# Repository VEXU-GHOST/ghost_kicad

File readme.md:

# VEXU GHOST PCB Repository

Welcome to UT IEEE RAS VEXU GHOST's repository for our PCB developments!
- [PCB Images](docs/pcb_images.md)
- [Onboarding](docs/onboarding.md)

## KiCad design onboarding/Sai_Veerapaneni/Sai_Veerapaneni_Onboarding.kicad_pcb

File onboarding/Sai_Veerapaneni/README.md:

# Sai Veerapaneni — PCB onboarding

Open `Sai_Veerapaneni_Onboarding.kicad_pro` in KiCad 10 to review the
color-sensor schematic and completed two-layer PCB.

The board is 26 × 18 mm, with 14 footprints, routed signal and supply nets,
front/back GND pours, and a rectangular Edge.Cuts outline. Signal tracks
are 0.2 mm; supply tracks are 0.3 mm with 0.2 mm sensor escapes. Copper
clearance is 0.2 mm and copper-to-edge clearance is 0.5 mm.

J1 pinout: **1 GND, 2 SCL, 3 SDA, 4 +3.3V, 5 +5V**. The host provides
both regulated supply rails. Sai Veerapaneni is printed on the back silk.

Custom libraries are project-local. Standard footprints and 3D models
use the installed KiCad libraries and this repository's `ghost_library`.
The connector preserves standard pads, drills, and physical geometry;
its off-board lead artwork is on F.Fab to keep silk inside the board edge.

Validation reports are saved in `checks/`. The schematic follows the
onboarding reference without power flags; the three external-supply ERC
errors are the ones the onboarding explicitly permits ignoring.

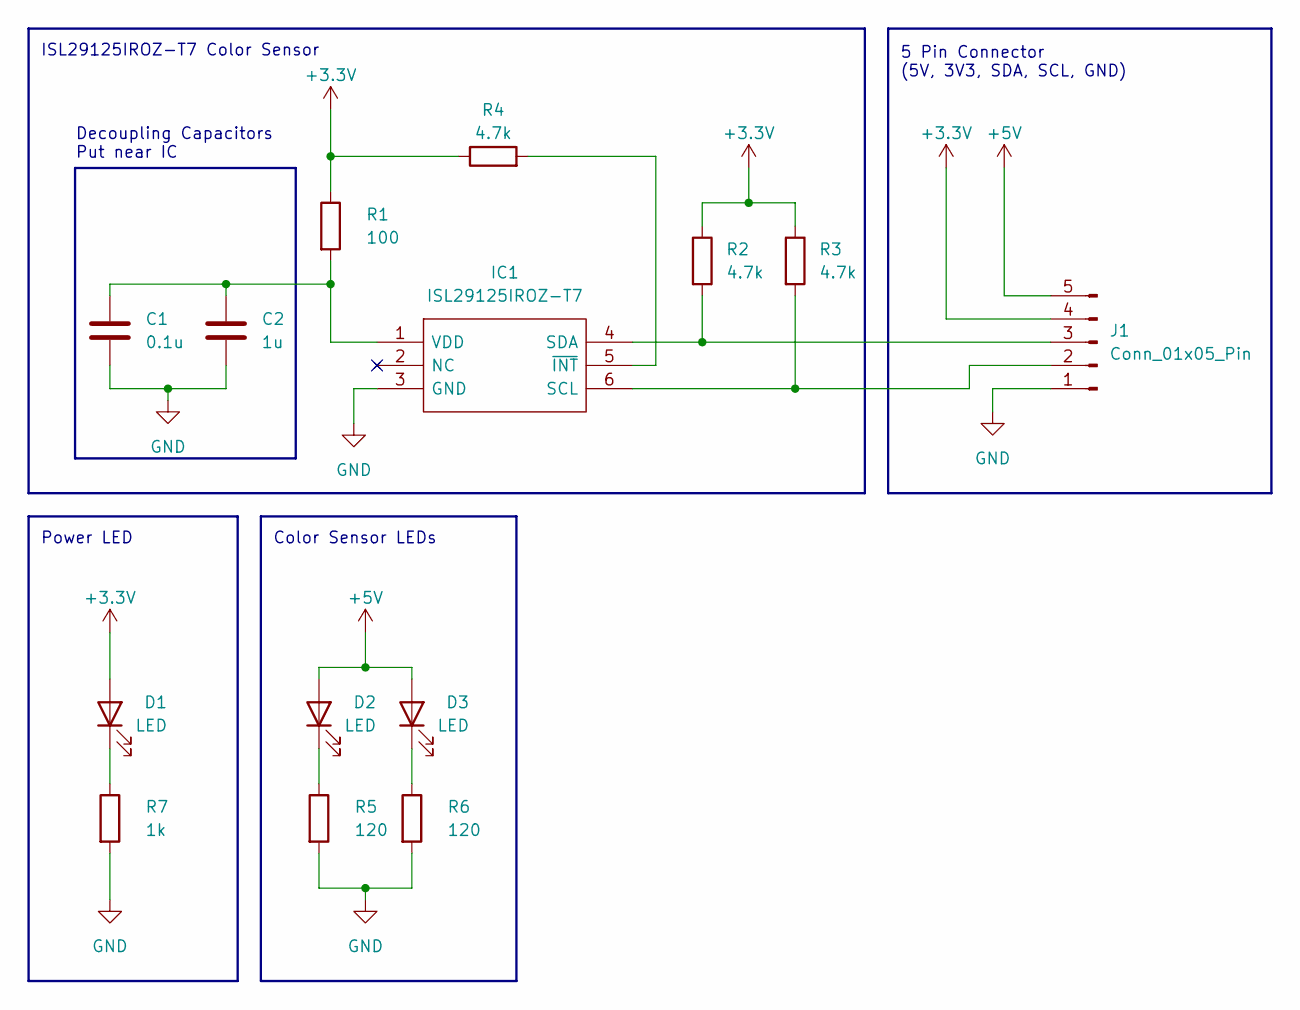
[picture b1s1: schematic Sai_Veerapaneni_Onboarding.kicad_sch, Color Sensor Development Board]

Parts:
C1: 0.1u; C_0603_1608Metric_Pad1.08x0.95mm_HandSolder
C2: 1u; C_0603_1608Metric_Pad1.08x0.95mm_HandSolder
D1: LED; LED_0603_1608Metric_Pad1.05x0.95mm_HandSolder
D2, D3: LED; LED_0805_2012Metric_Pad1.15x1.40mm_HandSolder
IC1: ISL29125IROZ-T7; ISL29125IROZT7; Manufacturer_Part_Number ISL29125IROZ-T7; Mouser Part Number 968-ISL29125IROZ-T7
J1: Conn_01x05_Pin; PinHeader_1x05_P2.54mm_Horizontal
R1: 100; R_0603_1608Metric_Pad0.98x0.95mm_HandSolder
R2, R3, R4: 4.7k; R_0603_1608Metric_Pad0.98x0.95mm_HandSolder
R5, R6: 120; R_0603_1608Metric_Pad0.98x0.95mm_HandSolder
R7: 1k; R_0603_1608Metric_Pad0.98x0.95mm_HandSolder

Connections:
+3.3V: D1.2 (A), J1.4, R1.1, R2.1, R3.1, R4.1
+5V: D2.2 (A), D3.2 (A), J1.5
GND: C1.2, C2.2, IC1.3 (GND), J1.1, R5.2, R6.2, R7.2
unnamed: D1.1 (K), R7.1
unnamed: D2.1 (K), R5.1
unnamed: D3.1 (K), R6.1
unnamed: IC1.6 (SCL), J1.2, R3.2
unnamed: IC1.4 (SDA), J1.3, R2.2
unnamed: C1.1, C2.1, IC1.1 (VDD), R1.2
unnamed: IC1.5 (~INT), R4.2

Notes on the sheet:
Color Sensor LEDs
Power LED
Decoupling Capacitors Put near IC
ISL29125IROZ-T7 Color Sensor
5 Pin Connector (5V, 3V3, SDA, SCL, GND)

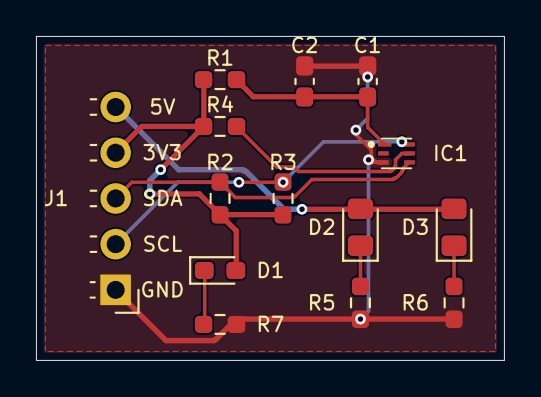
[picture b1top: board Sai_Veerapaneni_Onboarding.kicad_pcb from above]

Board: 2 copper layers, 26.0 x 18.0 mm, 14 parts (0 on the bottom side), 10 nets.

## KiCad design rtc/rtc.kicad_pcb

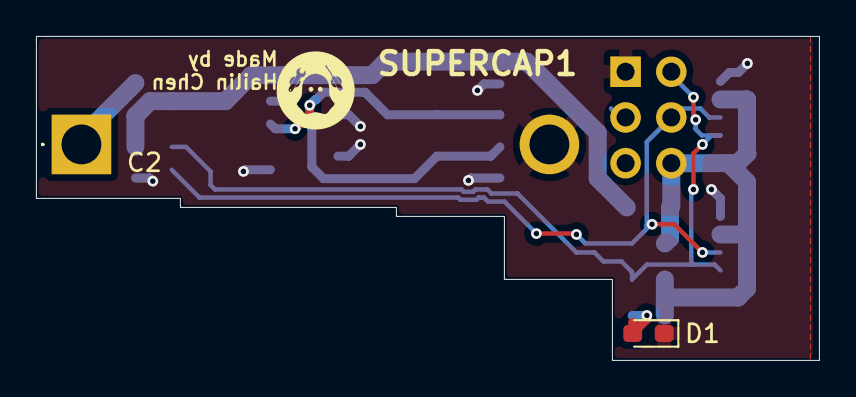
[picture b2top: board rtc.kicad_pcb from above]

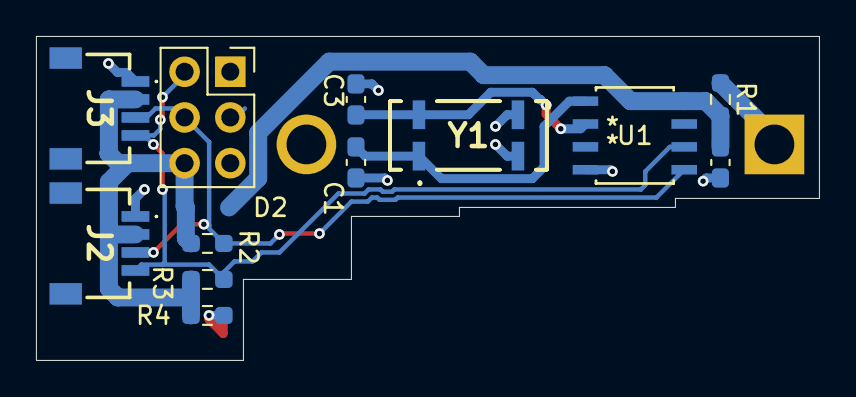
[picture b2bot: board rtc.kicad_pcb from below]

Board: 2 copper layers, 43.5 x 18.0 mm, 15 parts (13 on the bottom side), 9 nets.

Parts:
C1, C3: 24p; C_0603_1608Metric_Pad1.08x0.95mm_HandSolder
C2: 0.1u; C_0603_1608Metric_Pad1.08x0.95mm_HandSolder
D1: LED; LED_0603_1608Metric_Pad1.05x0.95mm_HandSolder
D2: RB751V-40X_R1; SODFL2512X90N
J1: Conn_02x03_Odd_Even; PinSocket_2x03_P2.54mm_Vertical
J2, J3: Conn_01x04; SM04BSRSSTB
R1: 20k; R_0603_1608Metric_Pad0.98x0.95mm_HandSolder
R2, R3, R4: 2.5k; R_0603_1608Metric_Pad0.98x0.95mm_HandSolder
SUPERCAP1: 5; CE5R5505HFZJ
U1: PCF8563T/5_518; PCF8563T_5_518_U_SO8_NXP
Y1: LFXTAL016178REEL

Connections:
+3.3V: D2.2 (A), J1.6, J2.2, J3.2, R2.2, R3.2, R4.1
GND: C1.2, C2.2, C3.2, D1.1 (K), J1.1, J2.1, J3.1, SUPERCAP1.2 (-), U1.4 (VSS), Y1.2 (N/C_1), Y1.3 (N/C_2)
unnamed: D1.2 (A), R4.2
unnamed: C2.1, D2.1 (K), R1.2, U1.8 (VDD)
unnamed: R1.1, SUPERCAP1.1 (+)
unnamed: C1.1, U1.1 (OSCI), Y1.1 (CRYSTAL_1)
unnamed: C3.1, U1.2 (OSCO), Y1.4 (CRYSTAL_2)
scl: J1.2, J2.4, J3.4, R3.1, U1.6 (SCL)
sda: J1.4, J2.3, J3.3, R2.1, U1.5 (SDA)

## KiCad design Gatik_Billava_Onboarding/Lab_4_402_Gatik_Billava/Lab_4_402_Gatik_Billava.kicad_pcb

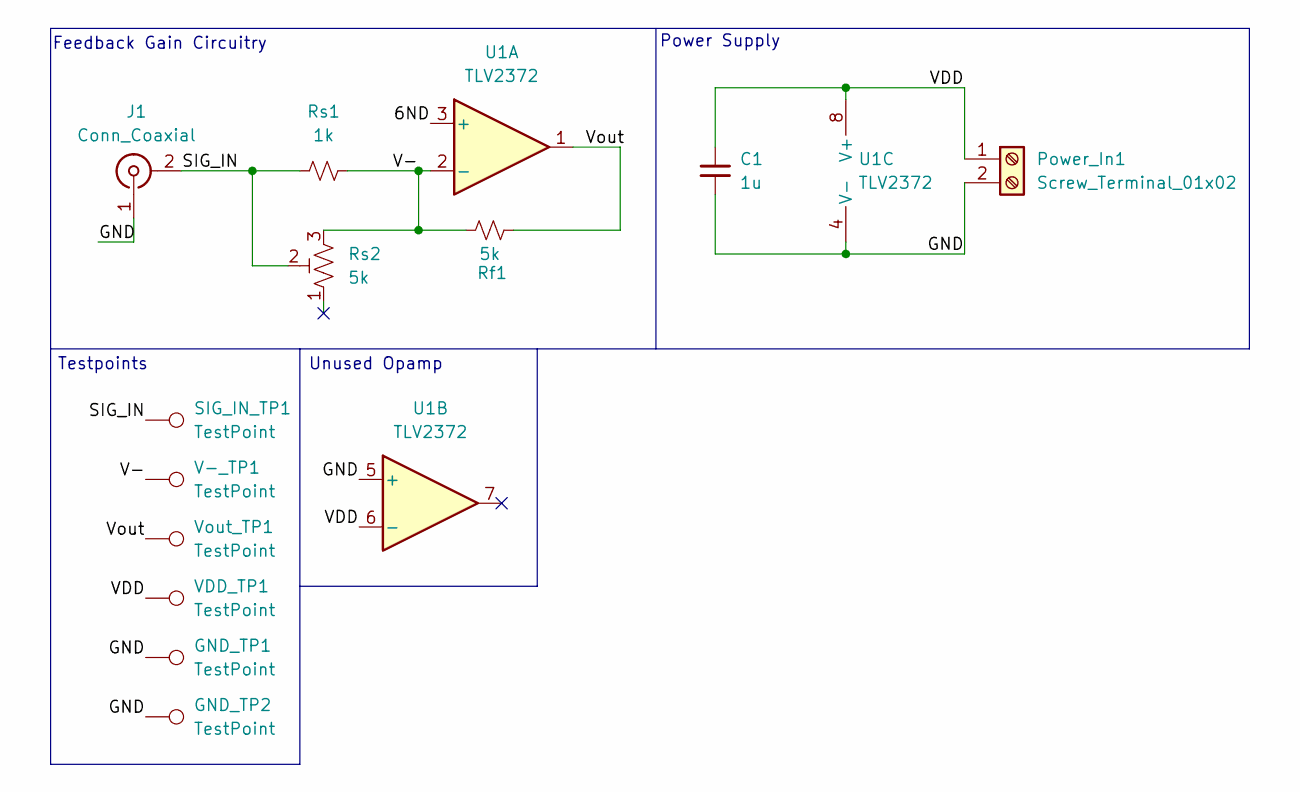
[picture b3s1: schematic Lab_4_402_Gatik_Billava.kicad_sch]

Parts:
C1: 1u; C_Disc_D3.8mm_W2.6mm_P2.50mm
GND_TP1, GND_TP2: TestPoint; TestPoint_Keystone_5010-5014_Multipurpose
J1: Conn_Coaxial; BNC_Amphenol_B6252HB-NPP3G-50_Horizontal
Power_In1: Screw_Terminal_01x02; PhoenixContact_MSTBA_2,5_2-G_1x02_P5.00mm_Horizontal
Rf1: 5k; R_Axial_DIN0207_L6.3mm_D2.5mm_P10.16mm_Horizontal
Rs1: 1k; R_Axial_DIN0207_L6.3mm_D2.5mm_P10.16mm_Horizontal
Rs2: 5k; Potentiometer_Vishay_43_Horizontal
SIG_IN_TP1: TestPoint; TestPoint_Keystone_5010-5014_Multipurpose
U1: TLV2372; SOIC-8_3.9x4.9mm_P1.27mm
V-_TP1: TestPoint; TestPoint_Keystone_5010-5014_Multipurpose
VDD_TP1: TestPoint; TestPoint_Keystone_5010-5014_Multipurpose
Vout_TP1: TestPoint; TestPoint_Keystone_5010-5014_Multipurpose

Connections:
/6ND: U1.3 (+)
/GND: C1.2, GND_TP1.1 (1_1), GND_TP2.1 (1_1), J1.1 (In), Power_In1.2, U1.4 (V-), U1.5 (+)
/SIG_IN: J1.2 (Ext), Rs1.1, Rs2.2, SIG_IN_TP1.1 (1_1)
/V-: Rf1.1, Rs1.2, Rs2.3, U1.2 (-), V-_TP1.1 (1_1)
/VDD: C1.1, Power_In1.1, U1.6 (-), U1.8 (V+), VDD_TP1.1 (1_1)
/Vout: Rf1.2, U1.1, Vout_TP1.1 (1_1)

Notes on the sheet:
Power Supply
Feedback Gain Circuitry
Unused Opamp
Testpoints

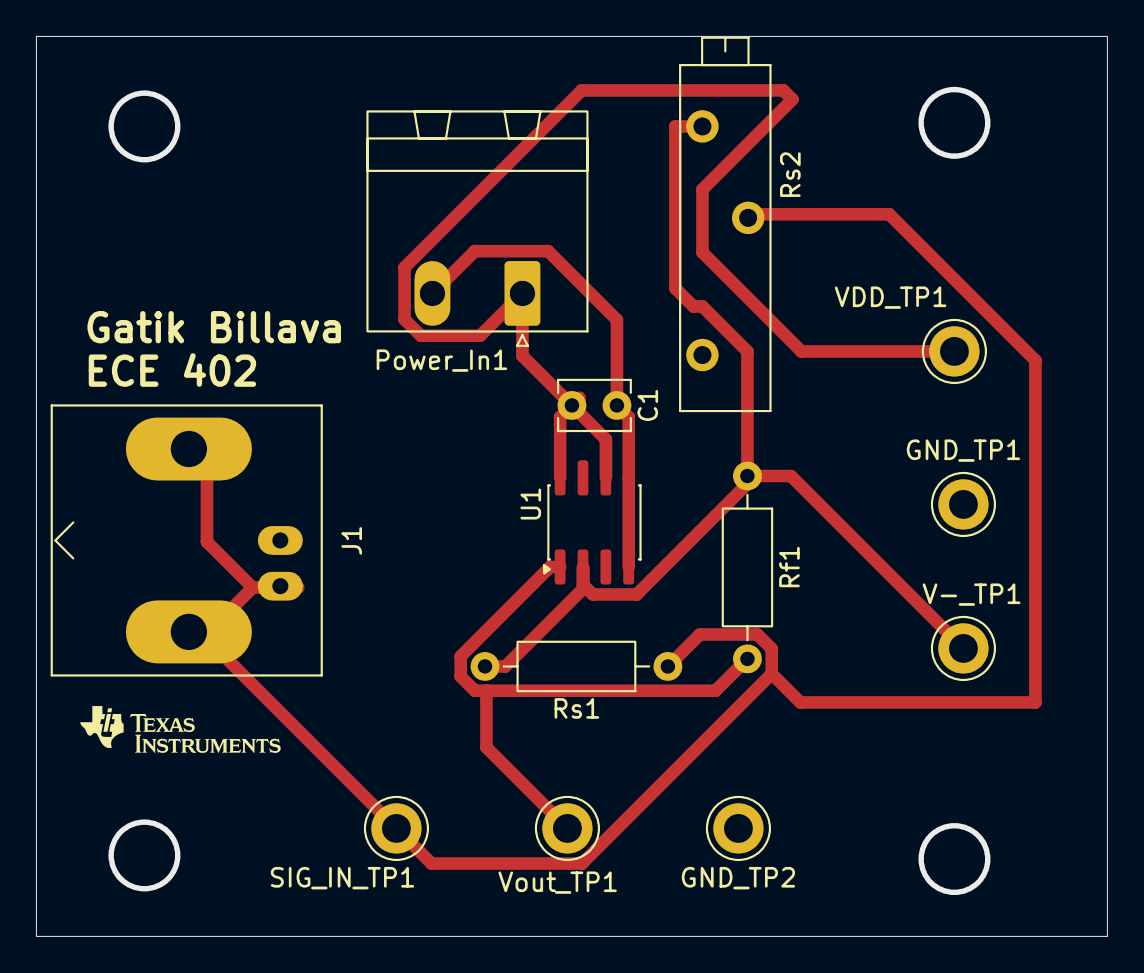
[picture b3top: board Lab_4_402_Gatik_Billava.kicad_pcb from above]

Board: 2 copper layers, 59.5 x 50.0 mm, 13 parts (0 on the bottom side), 5 nets.

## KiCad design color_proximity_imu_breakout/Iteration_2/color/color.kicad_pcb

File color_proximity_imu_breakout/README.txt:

color, imu, proximity.kicad files generated by hand from color+proximity.kicad_pcb

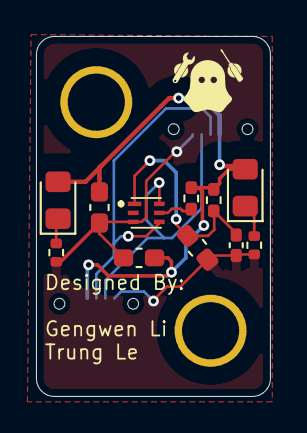
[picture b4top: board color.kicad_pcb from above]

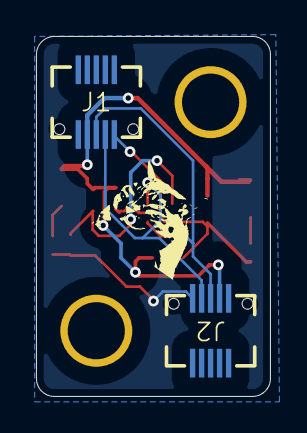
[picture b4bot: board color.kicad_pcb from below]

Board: 2 copper layers, 13.0 x 20.0 mm, 13 parts (2 on the bottom side), 8 nets.

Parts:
C1, C2: 10u; C_0603_1608Metric_Pad1.08x0.95mm_HandSolder
C4: 1u; C_0603_1608Metric_Pad1.08x0.95mm_HandSolder
C5: 0.1u; C_0402_1005Metric_Pad0.74x0.62mm_HandSolder
D1, D2: WHITE; LED_0805_2012Metric_Pad1.15x1.40mm_HandSolder
IC2: ISL29125IROZ-T7; ISL29125IROZT7
J1, J2: Conn_01x10; GT-B0502MSV27-10S1101
R15: 100; R_0402_1005Metric_Pad0.72x0.64mm_HandSolder
R16: 4.7k; R_0402_1005Metric_Pad0.72x0.64mm_HandSolder
R17, R18: 60; R_0402_1005Metric

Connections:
+3.3V: C1.1, C2.1, D1.2 (A), D2.2 (A), J1.7, J2.7, R15.2, R16.1
/scl: IC2.6 (SCL), J1.9, J2.9
/sda: IC2.4 (SDA), J1.8, J2.8
GND: C1.2, C2.2, C4.2, C5.2, IC2.3 (GND), J1.10, J2.10, R17.2, R18.2
unnamed: D1.1 (K), R17.1
unnamed: D2.1 (K), R18.1
unnamed: C4.1, C5.1, IC2.1 (VDD), R15.1
unnamed: IC2.5 (~INT), R16.2

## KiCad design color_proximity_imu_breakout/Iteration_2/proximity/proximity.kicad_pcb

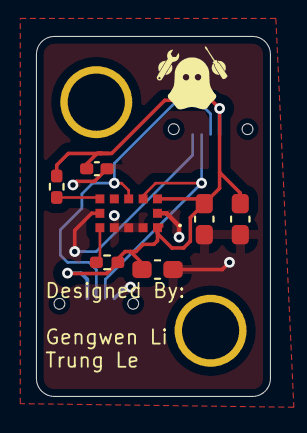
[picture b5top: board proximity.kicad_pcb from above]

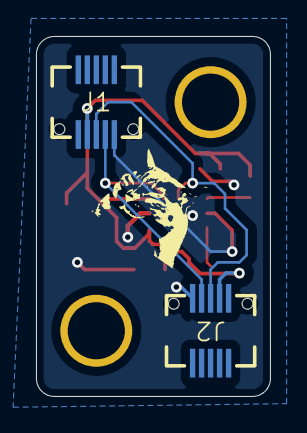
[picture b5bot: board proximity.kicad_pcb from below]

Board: 2 copper layers, 13.0 x 20.0 mm, 9 parts (2 on the bottom side), 6 nets.

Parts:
C1, C2: 10u; C_0603_1608Metric_Pad1.08x0.95mm_HandSolder
C11: 0.1u; C_0402_1005Metric_Pad0.74x0.62mm_HandSolder
C12: 4.7u; C_0603_1608Metric_Pad1.08x0.95mm_HandSolder
IC1: VL53L4CDV0DH_1; VL53L4CDV0DH1
J1, J2: Conn_01x10; GT-B0502MSV27-10S1101
R20, R21: 10k; R_0402_1005Metric_Pad0.72x0.64mm_HandSolder

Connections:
+3.3V: C1.1, C2.1, C11.1, C12.1, IC1.1 (AVDDVCSEL_1), IC1.11 (AVDD), IC1.13 (AVDDVCSEL_2), J1.7, J2.7, R20.2, R21.1
/scl: IC1.10 (SCL), J1.9, J2.9
/sda: IC1.9 (SDA), J1.8, J2.8
GND: C1.2, C2.2, C11.2, C12.2, IC1.2 (AVSSVCSEL), IC1.3 (GND), IC1.4 (GND2), IC1.6 (GND3), IC1.12 (GND4), J1.10, J2.10
unnamed: IC1.7 (GPIO1), R20.1
unnamed: IC1.5 (XSHUT), R21.2

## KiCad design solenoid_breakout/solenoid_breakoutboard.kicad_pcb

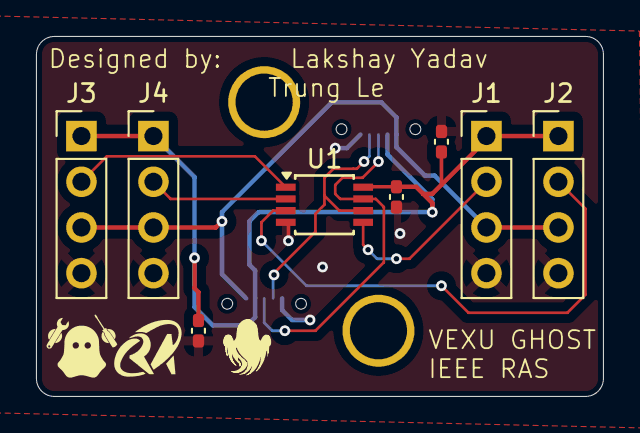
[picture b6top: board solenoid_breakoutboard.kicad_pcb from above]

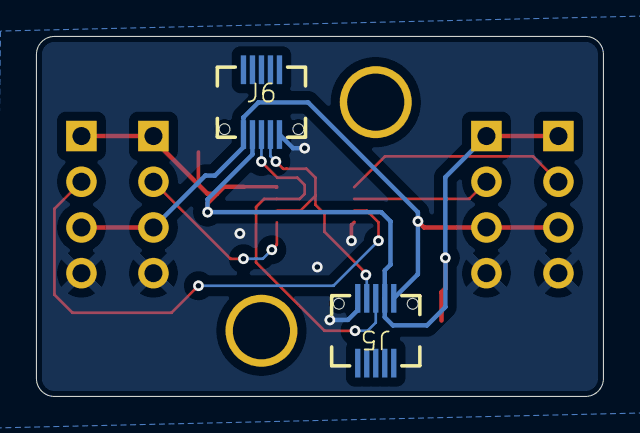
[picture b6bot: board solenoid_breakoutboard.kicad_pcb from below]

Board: 2 copper layers, 31.5 x 20.0 mm, 10 parts (2 on the bottom side), 9 nets.

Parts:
C1: 0.1uF; C_0402_1005Metric_Pad0.74x0.62mm_HandSolder
C2, C3: 10uF; C_0402_1005Metric_Pad0.74x0.62mm_HandSolder
J1, J2, J3, J4: Conn_01x04_Pin; PinHeader_1x04_P2.54mm_Vertical
J5, J6: Conn_01x10; GT-B0502MSV27-10S1101
U1: TCA9536DTMR; TSSOP-8_3x3mm_P0.65mm

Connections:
+3.3V: C1.1, C2.1, C3.1, J1.1, J2.1, J3.1, J4.1, J5.7, J6.7, U1.8 (VDD)
+5V: J1.3, J2.3, J3.3, J4.3, J5.6, J6.6
/scl: J5.9, J6.9, U1.6 (SCL)
/sda: J5.8, J6.8, U1.7 (SDA)
GND: C1.2, C2.2, C3.2, J1.4, J2.4, J3.4, J4.4, J5.10, J6.10, U1.4 (VSS)
unnamed: J1.2, U1.5 (IO3)
unnamed: J2.2, U1.3 (IO2)
unnamed: J3.2, U1.1 (IO0)
unnamed: J4.2, U1.2 (IO1)

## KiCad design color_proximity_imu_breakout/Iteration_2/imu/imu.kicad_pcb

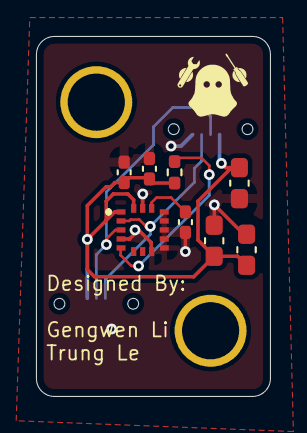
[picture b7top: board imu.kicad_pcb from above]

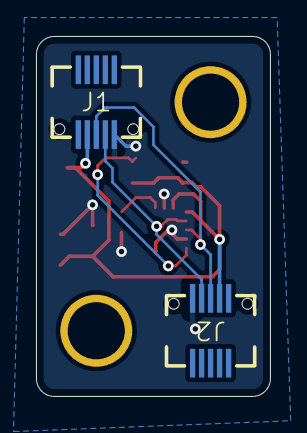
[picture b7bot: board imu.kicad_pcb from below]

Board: 2 copper layers, 13.0 x 20.0 mm, 10 parts (2 on the bottom side), 6 nets.

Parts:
C1, C2: 10u; C_0603_1608Metric_Pad1.08x0.95mm_HandSolder
C7, C10: 0.1u; C_0402_1005Metric_Pad0.74x0.62mm_HandSolder
C8: 2.2u; C_0603_1608Metric_Pad1.08x0.95mm_HandSolder
C9: 10n; C_0402_1005Metric_Pad0.74x0.62mm_HandSolder
J1, J2: Conn_01x10; GT-B0502MSV27-10S1101
R19: 4.7k; R_0402_1005Metric_Pad0.72x0.64mm_HandSolder
U6: ICM-20602; IAM20680HP

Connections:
+3.3V: C1.1, C2.1, C7.1, C8.1, C9.1, J1.7, J2.7, R19.1, U6.1 (VDDIO), U6.16 (VDD)
/scl: J1.9, J2.9, U6.2 (SCL/SPC)
/sda: J1.8, J2.8, U6.3 (SDA/SDI)
GND: C1.2, C2.2, C7.2, C8.2, C9.2, C10.2, J1.10, J2.10, U6.4 (SAO/SD0), U6.8 (FSYNC), U6.9 (GND), U6.10 (GND), U6.11 (GND), U6.12 (GND), U6.13 (GND), U6.15 (GND)
unnamed: C10.1, U6.14 (REGOUT)
unnamed: R19.2, U6.5 (~CS)

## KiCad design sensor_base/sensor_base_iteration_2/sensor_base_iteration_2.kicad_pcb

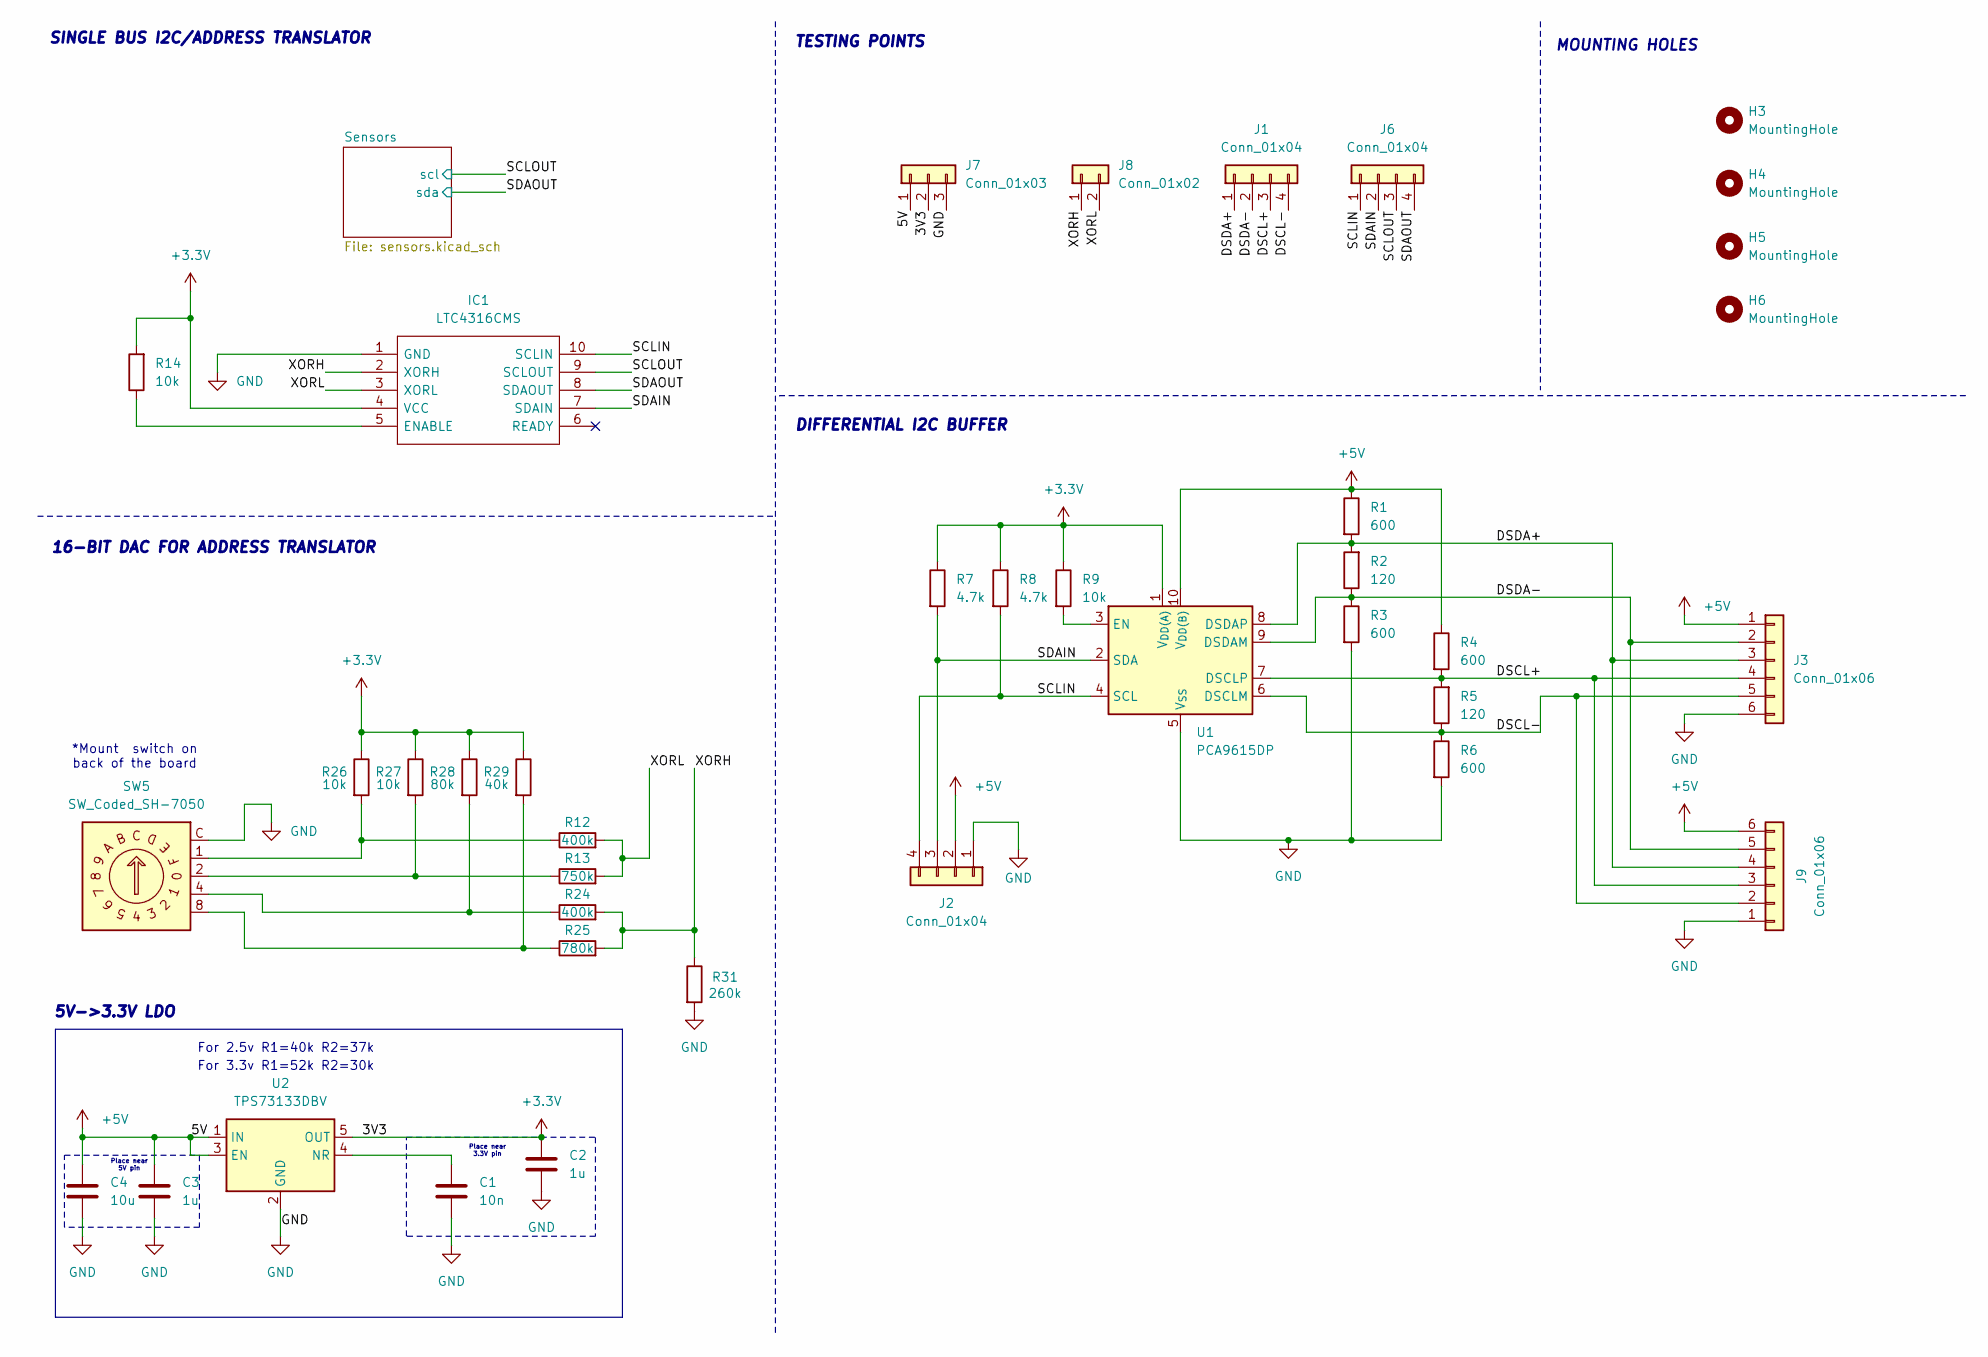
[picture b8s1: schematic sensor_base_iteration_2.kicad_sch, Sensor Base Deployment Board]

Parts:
C1: 10n; C_0402_1005Metric_Pad0.74x0.62mm_HandSolder; Manufacturer_Part_Number CL05B103KB5NNNC; JLCPCB Part C1523
C2, C3: 1u; C_0603_1608Metric_Pad1.08x0.95mm_HandSolder; Manufacturer_Part_Number CL10B105KB8NQNC; JLCPCB Part C15849
C4: 10u; C_0603_1608Metric_Pad1.08x0.95mm_HandSolder; Manufacturer_Part_Number CL10A106KP8NNNC; JLCPCB Part C15849
H3, H4, H5, H6: MountingHole; MountingHole_#4_3.175mm
IC1: LTC4316CMS; SOP50P490X110-10N; Manufacturer_Part_Number LTC4316CMS#TRPBF; Mouser Part Number 584-LTC4316CMS#TRPBF
J1, J6: Conn_01x04; PinHeader_1x04_P1.27mm_Vertical
J2: Conn_01x04; JST_GH_SM04B-GHS-TB_1x04-1MP_P1.25mm_Horizontal; Manufacturer_Part_Number XY-SM04B-GHS-TB; JLCPCB Part C51940130
J3, J9: Conn_01x06; JST_GH_SM06B-GHS-TB_1x06-1MP_P1.25mm_Horizontal; Manufacturer_Part_Number XY-SM06B-GHS-TB; JLCPCB Part C160405
J7: Conn_01x03; PinHeader_1x03_P1.27mm_Vertical
J8: Conn_01x02; PinHeader_1x02_P1.27mm_Vertical
R1, R3, R4, R6: 600; R_0402_1005Metric_Pad0.72x0.64mm_HandSolder; Manufacturer_Part_Number 0402WGF6040TCE; JLCPCB Part 0402WGF6040TCE
R2, R5: 120; R_0402_1005Metric_Pad0.72x0.64mm_HandSolder; Manufacturer_Part_Number 0402WGF1200TCE; JLCPCB Part 0402WGF1200TCE
R7, R8: 4.7k; R_0402_1005Metric_Pad0.72x0.64mm_HandSolder; Manufacturer_Part_Number 0402WGF4701TCE; JLCPCB Part 0402WGF4701TCE
R9, R14, R26, R27: 10k; R_0402_1005Metric_Pad0.72x0.64mm_HandSolder; Manufacturer_Part_Number 0402WGF1002TCE; JLCPCB Part 0402WGF1002TCE
R12, R24: 400k; R_0402_1005Metric_Pad0.72x0.64mm_HandSolder; Manufacturer_Part_Number 0402WGF4023TCE; JLCPCB Part 0402WGF4023TCE
R13: 750k; R_0402_1005Metric_Pad0.72x0.64mm_HandSolder; Manufacturer_Part_Number 0402WGF7503TCE; JLCPCB Part 0402WGF7503TCE
R25: 780k; R_0402_1005Metric_Pad0.72x0.64mm_HandSolder; Manufacturer_Part_Number 0402WGF7873TCE; JLCPCB Part 0402WGF7873TCE
R28: 80k; R_0402_1005Metric_Pad0.72x0.64mm_HandSolder; Manufacturer_Part_Number NQ02WGF8062TCE; JLCPCB Part NQ02WGF8062TCE
R29: 40k; R_0402_1005Metric_Pad0.72x0.64mm_HandSolder; Manufacturer_Part_Number 0402WGF4022TCE; JLCPCB Part 0402WGF4022TCE
R31: 260k; R_0402_1005Metric_Pad0.72x0.64mm_HandSolder; Manufacturer_Part_Number 0402WGF2613TCE; JLCPCB Part 0402WGF2613TCE
SW5: SW_Coded_SH-7050; Rotary_Switch_16_pos; Manufacturer_Part_Number ES07MH-16RBZ-L1000
U1: PCA9615DP; TSSOP-10_3x3mm_P0.5mm; Manufacturer_Part_Number PCA9615DP; JLCPCB Part PCA9615DP
U2: TPS73133DBV; SOT-23-5; Manufacturer_Part_Number TPS73133DBVR

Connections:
+3.3V: C2.1, IC1.4 (VCC), J7.2, R7.1, R8.1, R9.1, R14.2, R26.1, R27.1, R28.1, R29.1, U1.1 (V_{DD(A)}), U2.5 (OUT); also elsewhere on the board
+5V: C3.1, C4.1, J2.2, J3.1, J7.1, J9.6, R1.1, R4.1, U1.10 (V_{DD(B)}), U2.1 (IN), U2.3 (EN); also elsewhere on the board
/DSCL+: J1.3, J3.4, J9.3, R4.2, R5.2, U1.7 (DSCLP)
/DSCL-: J1.4, J3.5, J9.2, R5.1, R6.1, U1.6 (DSCLM)
/DSDA+: J1.1, J3.3, J9.4, R1.2, R2.2, U1.8 (DSDAP)
/DSDA-: J1.2, J3.2, J9.5, R2.1, R3.1, U1.9 (DSDAM)
/SCLIN: IC1.10 (SCLIN), J2.4, J6.1, R8.2, U1.4 (SCL)
/SCLOUT: IC1.9 (SCLOUT), J6.3; also elsewhere on the board
/SDAIN: IC1.7 (SDAIN), J2.3, J6.2, R7.2, U1.2 (SDA)
/SDAOUT: IC1.8 (SDAOUT), J6.4; also elsewhere on the board
/XORH: IC1.2 (XORH), J8.1, R24.2, R25.2, R31.1
/XORL: IC1.3 (XORL), J8.2, R12.2, R13.2
GND: C1.2, C2.2, C3.2, C4.2, IC1.1 (GND), J2.1, J3.6, J7.3, J9.1, R3.2, R6.2, R31.2, SW5.C, U1.5 (V_{SS}), U2.2 (GND); also elsewhere on the board
unnamed: IC1.5 (ENABLE), R14.1
unnamed: R12.1, R26.2, SW5.1
unnamed: R13.1, R27.2, SW5.2
unnamed: R24.1, R28.2, SW5.4
unnamed: R25.1, R29.2, SW5.8
unnamed: R9.2, U1.3 (EN)
unnamed: C1.1, U2.4 (NR)

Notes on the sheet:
16-BIT DAC FOR ADDRESS TRANSLATOR
*Mount switch on back of the board
TESTING POINTS
5V->3.3V LDO
MOUNTING HOLES
For 2.5v R1=40k R2=37k
DIFFERENTIAL I2C BUFFER
Place near 5V pin
Place near 3.3V pin
For 3.3v R1=52k R2=30k
SINGLE BUS I2C/ADDRESS TRANSLATOR

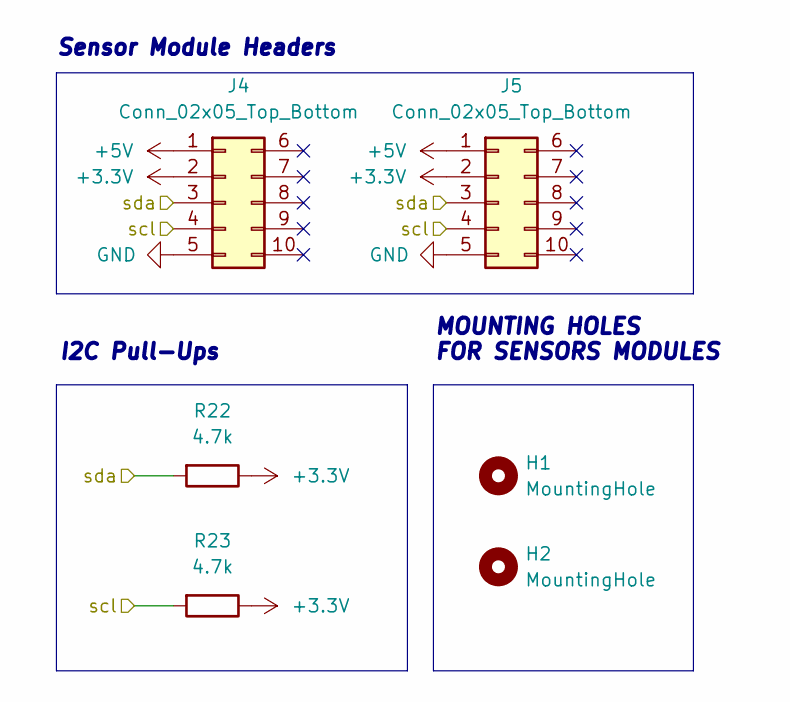
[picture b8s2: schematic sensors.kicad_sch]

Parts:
H1, H2: MountingHole; MountingHole_#4_3.175mm
J4, J5: Conn_02x05_Top_Bottom; GT-B0502FSV43-10S1101; Manufacturer_Part_Number GT-B0502FSV43-10S1101
R22, R23: 4.7k; R_0402_1005Metric_Pad0.72x0.64mm_HandSolder; Manufacturer_Part_Number 0402WGF4701TCE; JLCPCB Part 0402WGF4701TCE

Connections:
+3.3V: J4.2, J5.2, R22.1, R23.1; also elsewhere on the board
+5V: J4.1, J5.1; also elsewhere on the board
/SCLOUT: J4.4, J5.4, R23.2; also elsewhere on the board
/SDAOUT: J4.3, J5.3, R22.2; also elsewhere on the board
GND: J4.5, J5.5; also elsewhere on the board

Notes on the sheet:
Sensor Module Headers
MOUNTING HOLES FOR SENSORS MODULES
I2C Pull-Ups

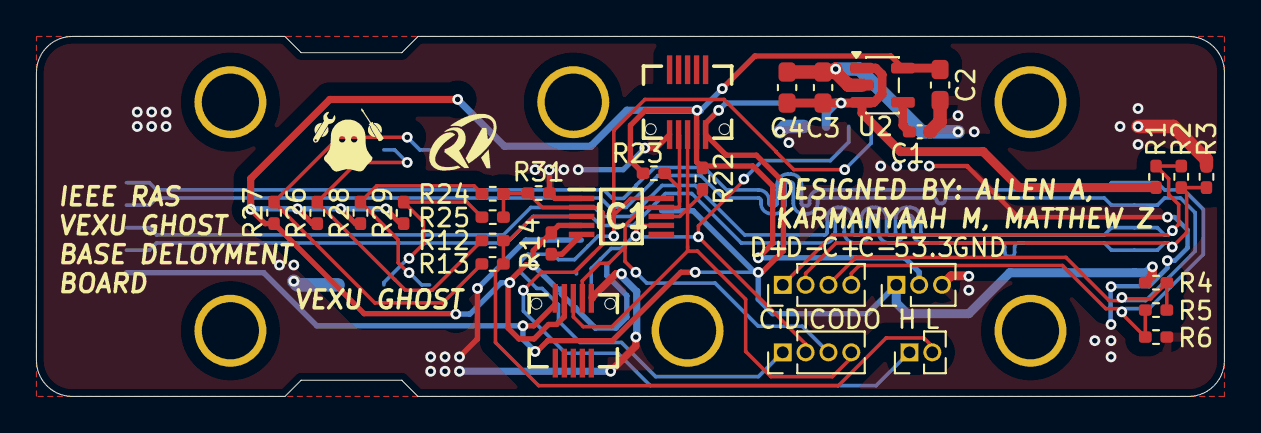
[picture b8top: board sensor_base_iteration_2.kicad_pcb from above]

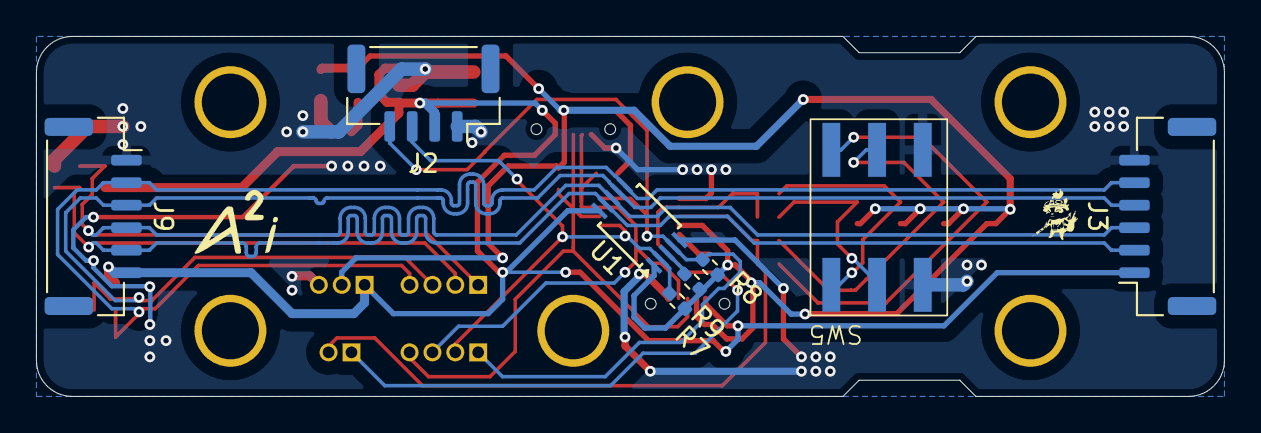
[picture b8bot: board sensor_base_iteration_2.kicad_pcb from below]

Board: 2 copper layers, 66.0 x 20.0 mm, 44 parts (8 on the bottom side), 20 nets.

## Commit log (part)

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2025-09-04 add sensor
2025-09-04 host changes 9/4
2025-09-07 update sensor
2025-09-13 updated sensor
2025-09-13 switched out raspPi pico to kb2040, added RGB connector, assigned footprints, created RJ12 footprint
2025-09-14 import kb2040 footprint, made RJ12 pin footprint
2025-09-14 RJ12 connector footprint assigned
2025-09-14 karmanyaah's footprints
2025-09-14 added RJ12 footprint to sensor
2025-09-14 new tca9536 footprint
2025-09-14 updated resistor footprint, began pcb layout
2025-09-14 updated resistor footprints, began prb layout
2025-09-14 added DAC without offset
2025-09-15 remerge
2025-09-20 finished host board PCB layout
2025-09-21 created slide switch footprint, assigned resistor and switch footprints
2025-09-21 idk what i changed
2025-09-27 updated RJ12 pin holes to ooblong
2025-09-27 updated DAC and started board placement
2025-09-27 created footprint for rotary switch
2025-09-28 make things nicerg
2025-09-28 reorg pcb layout
2025-09-28 half way done with board
2025-10-04 began wiring PCB
2025-10-04 RJ12 connector 3D model
2025-10-05 3d models
2025-10-05 why did the lck files change
2025-10-05 finished host board
2025-10-05 labels added to Host board
2025-10-05 remove unneceesary models
2025-10-05 pcb review, added 3d models
2025-10-05 rearranged some parts
2025-10-05 finished traces but forgor output RJ12
2025-10-06 finished board pre adding output RJ12
2025-10-12 more formatting
2025-10-12 fixed edge cut layer
2025-10-12 added new sensor files
2025-10-12 new proximity sensor schematic + output RJ12 connectore (pls double check this im just assuming they connect in series)
2025-10-12 update color sensor
2025-10-13 added footprints of new sensors and JST/RJ12 connectors into PCB
2025-10-21 switch
2025-10-21 added pcb
2025-10-21 switch with all files found in the folder
2025-10-21 finalize comp switch
2025-10-21 switch move
2025-10-23 restarting layout
2025-10-24 sensor pcb layout, deleted gpio ic
2025-10-24 host w/ bom
2025-10-24 sensor pcb layout
2025-10-24 sensor BOM
2025-10-24 what
2025-10-25 BOM added capacitors
2025-10-25 Add BOM; Add LED; change LTC footprint
2025-10-26 bom stuff
2025-10-26 added solenoid driver board folder and kicad project
2025-10-30 new breakout directory
2025-10-31 not my finest work but at least it works (i hope)
2025-10-31 minimizing sensor main board
2025-11-02 jOHUGYIFUG#CH@VDJIOwewfurhgvwbdjqnkdiofrguhybfedwqnskjmlidorfguthefdwjqnk2
2025-11-02 added imu breakout project and solenoid driver breakout project
2025-11-02 i hate git
2025-11-02 aded stuf
2025-11-02 just the proximity sensor
2025-11-03 finished main sensor board
2025-11-03 forgot to save schematic
2025-11-04 add caps to host; make sensor_breakouts larger; update bom & generated production files for everything
2025-11-09 cleaned up directory with single project folders and centralized library folder for symbols, footprints, and 3d models
2025-11-09 step files
2025-11-16 additional symbol and footprint clean up
2025-11-17 finished solenoid breakout schematic + started on PCB
2025-11-17 started on rtc
2025-11-17 rtc progress
2025-11-17 solenoid breakout design finished awaiting review
2025-11-18 small fixes
2025-11-24 rtc schematic progress
2025-11-29 finished rtc schematic
2025-12-04 finished rtc pcb
2025-12-05 rtc pcb iteration 2
2025-12-23 finished rtc board + sensor base 3d model change
2026-01-07 minor rtc change
2026-01-07 revised solenoid board
2026-01-08 updated readme + pcb images
2026-01-08 minor change
2026-01-08 pushed what I had done so far for the power management board(sorry for how I titled it)
2026-01-12 removed solenoid driver and fixed pcb file issue
2026-01-12 added charging pcb project and minor changed to host schematic
2026-01-16 physical board images + readme update
2026-01-25 added onboarding and fixed pcb models
2026-01-25 organized readme
2026-01-25 readme minor fix
2026-01-25 finished onboarding
2026-01-26 onboarding fix
2026-01-26 onboarding change
2026-02-04 updated onboarding and rtc crystal model change
2026-02-04 onboarding code block change
2026-02-04 onboarding code block change 2
2026-02-04 onboarding code block change 3
2026-02-04 onboarding code block change 4
2026-02-04 onboarding code block change 5
2026-03-09 updated base board + updated gpio breakout + added bom/fab files
2026-03-15 Iteration 2 of color, distance, and imu sensor boards
2026-03-15 GPIO Iteration 2 changes
2026-03-16 reorganized base board dir with iteration 1 and iteration 2, added TCA9536DGKR symbol, footprint, and 3d model
2026-03-18 added symbols, footprints, and 3d models of sm04b gh and sm06b gh jst connectors
2026-03-19 finished base board interation 2 schematic and started on pcb layout
2026-03-22 added power stability simulation files and board to board connector 3d models
2026-03-22 Color Board Iteration 2 Updated
2026-03-22 imu updated iteration 2
2026-03-22 imu board iteration 2 updated
2026-03-22 proximity board iteration 2 updated
2026-03-22 gpio board iteration 2 updated
2026-03-22 breakout board iteration 2 updates
2026-03-23 gpio iteration 2 update
2026-03-23 finished base board PCB + created production files for base board and modules
2026-03-24 a
    a
2026-03-24 Revert "Update ghost_host.kicad_pcb"
    This reverts commit c9f05f9862b4d82e3d53fd6de1de5a61cf89d8c6.
2026-03-24 Revert "a"
    This reverts commit 4ec56b0c7e850830ef165470b753964675e311dd.
2026-03-24 please fix everything
2026-03-25 started host board layout v2
2026-03-26 host board updated
2026-03-26 finish host board v2 layout + production files
2026-03-28 updated host schematic and imu production files
2026-04-01 updated production files
